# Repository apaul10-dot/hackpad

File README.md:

# FootyPad

This hackpad is for soccer players and gamers, something that I am. It is desinged for soccer related games such as FIFA in which the buttons can be used for functions such as moving and scoring goals. I found my inspiration for this hackpad through my love of soccer and the game of FIFA. 

---

## Images

### Assembly

### Case (3D Printed)

### Schematic

### PCB Layout

---

##  Bill of Materials
| Item | Description | Quantity | Size/Package | Purchase Link | Notes |
|------|-------------|----------|--------------|---------------|-------|
| U1 | XIAO RP2040 Microcontroller | 1 | DIP | [Seeed Studio](https://www.seeedstudio.com/XIAO-RP2040-v1-0-p-5026.html) \| [Adafruit](https://www.adafruit.com/product/4900) | Seeed Studio XIAO RP2040 |
| SW1-SW6 | Tactile Push Button Switch | 6 | SW_Push | [Adafruit](https://www.adafruit.com/product/367) \| [SparkFun](https://www.sparkfun.com/products/97) | 6x6mm momentary pushbutton switches |
| SW4 | Rotary Encoder with Switch | 1 | RotaryEncoder_Switch | [Adafruit](https://www.adafruit.com/product/377) \| [SparkFun](https://www.sparkfun.com/products/9117) | EC11 type rotary encoder with integrated pushbutton |
| Enclosure | 3D Printed Housing | 1 | PLA/PETG | [Thingiverse](https://www.thingiverse.com) \| [Printables](https://www.printables.com) | Orange colored housing as shown - STL files needed |
| PCB | Custom PCB | 1 | FR4 | [JLCPCB](https://jlcpcb.com) \| [PCBWay](https://www.pcbway.com) | Custom designed PCB - Gerber files needed |
| Screws | Machine screws | 4-8 | M3 x 6mm | [McMaster-Carr](https://www.mcmaster.com) \| [Amazon](https://www.amazon.com/s?k=M3+screws) | For PCB mounting and enclosure as

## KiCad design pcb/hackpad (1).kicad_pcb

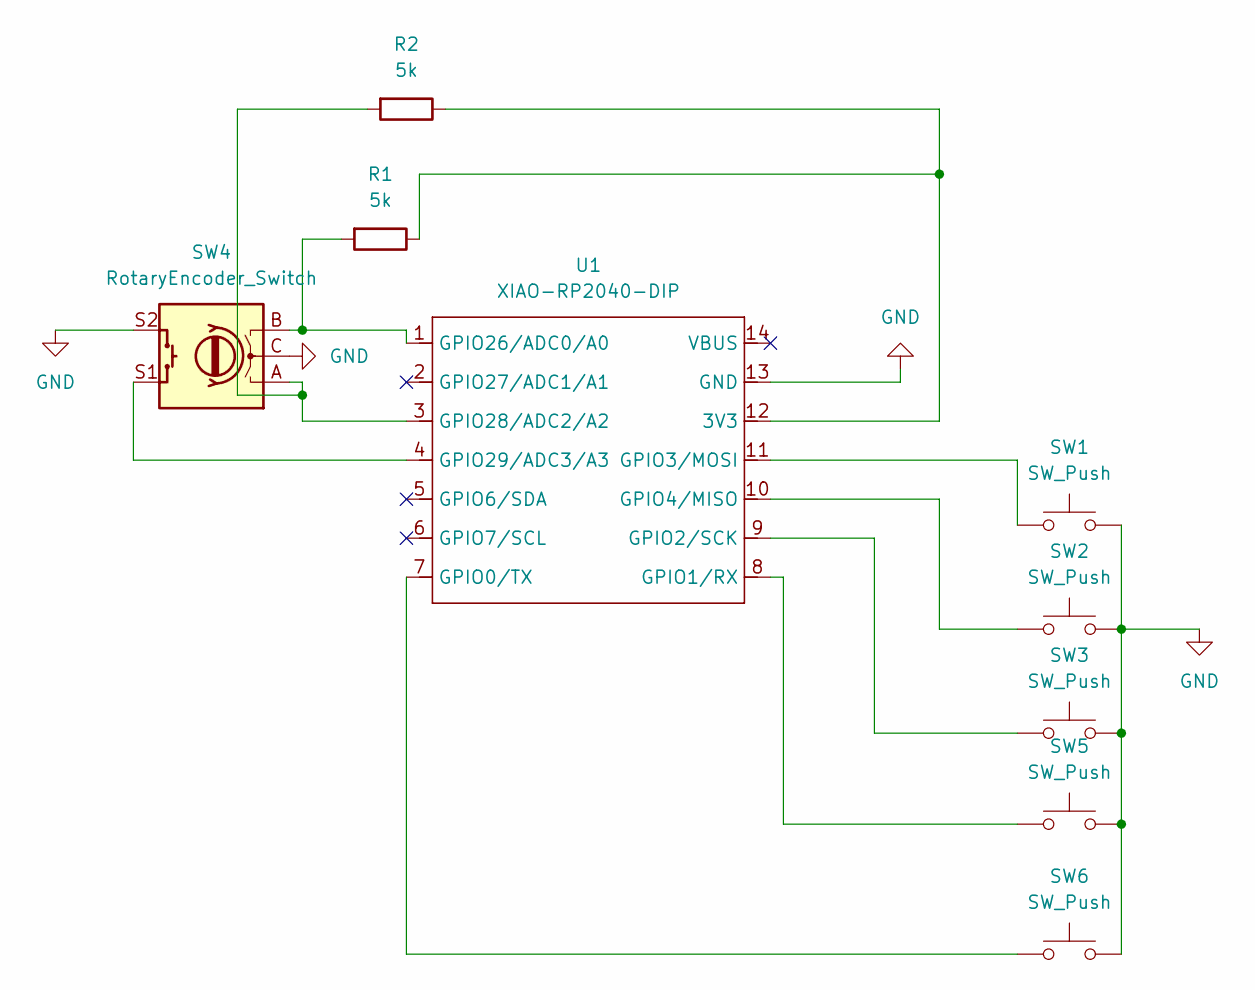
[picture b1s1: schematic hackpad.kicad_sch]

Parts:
R1, R2: 5k; R_Axial_DIN0204_L3.6mm_D1.6mm_P7.62mm_Horizontal
SW1, SW2, SW3: SW_Push; SW_Cherry_MX_1.00u_PCB
SW4: RotaryEncoder_Switch; RotaryEncoder_Alps_EC11E-Switch_Vertical_H20mm_CircularMoun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
SW5, SW6: SW_Push; SW_PUSH_6mm_H9.5mm
U1: XIAO-RP2040-DIP

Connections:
GND: SW1.2, SW2.2, SW3.2, SW4.C, SW4.S2, SW5.2, SW6.2, U1.13 (GND)
unnamed: R1.1, R2.1, U1.12 (3V3)
unnamed: SW6.1, U1.7 (GPIO0/TX)
unnamed: SW5.1, U1.8 (GPIO1/RX)
unnamed: SW3.1, U1.9 (GPIO2/SCK)
unnamed: SW1.1, U1.11 (GPIO3/MOSI)
unnamed: SW2.1, U1.10 (GPIO4/MISO)
unnamed: R1.2, SW4.B, U1.1 (GPIO26/ADC0/A0)
unnamed: R2.2, SW4.A, U1.3 (GPIO28/ADC2/A2)
unnamed: SW4.S1, U1.4 (GPIO29/ADC3/A3)

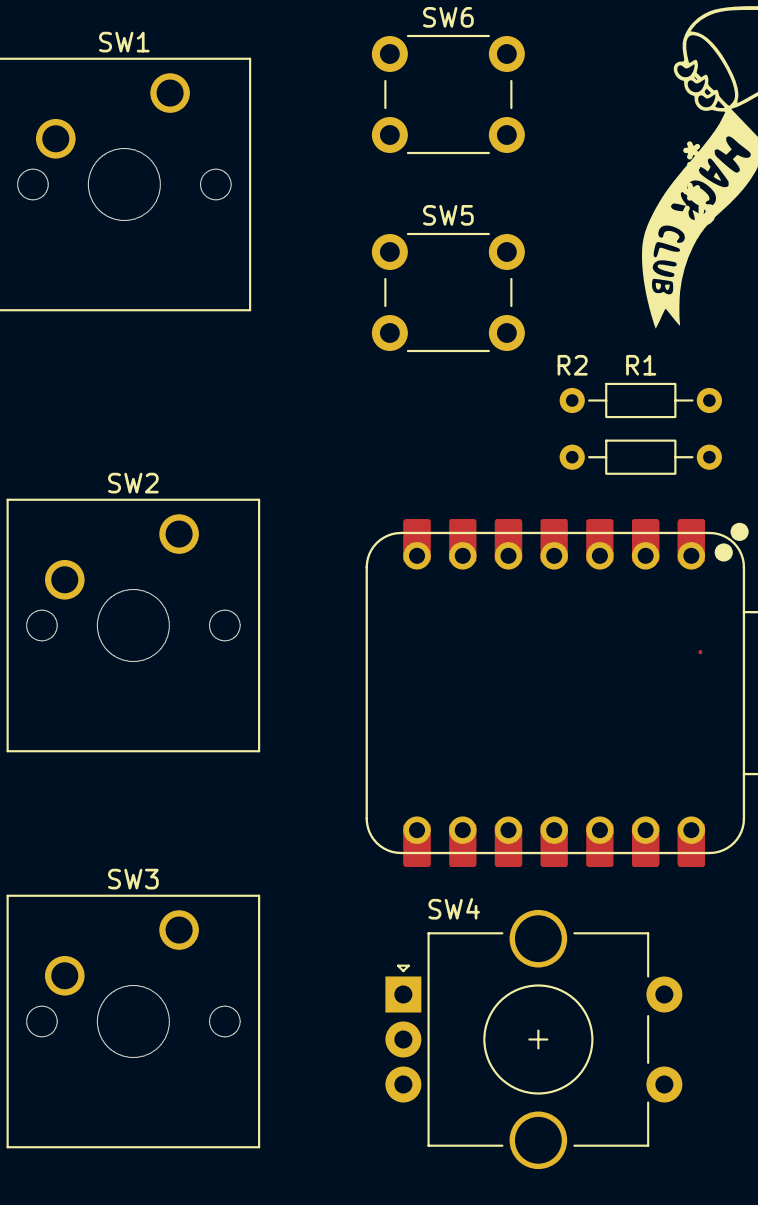
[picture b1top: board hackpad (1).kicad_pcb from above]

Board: 2 copper layers, 9 parts (0 on the bottom side), 10 nets.

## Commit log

2025-06-29 Adding firmware
2025-06-29 Fixing some stuff
2025-06-29 Rename MIDDLE.stl to CASE.stl
2025-06-29 Putting things into folders
2025-06-29 Finalizing changes
2025-06-30 Updating readme
2025-07-07 Rename hackpad_cad.stl to hackpad_cad.step
2025-07-07 Changing assets
2025-07-08 Changing CAD
2025-07-08 Fixing CAD
